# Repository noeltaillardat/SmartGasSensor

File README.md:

# SmartGasSensor
#### Arduino shield with gas sensing and LoRa connection.

On this github, you will find KiCad files to print your PCB and Arduino files to upload code to use the shield.

## Functionalities
* Gas sensor + Electrical noise reduction + Temperature setting
* Warning trigger + visual warning 
* LoRa communication + TTN connection
* Buzzer can be activated

### Gas sensor + Electrical noise reduction
Gas sensor made at the AIME whiteroom of Toulouse.

On the shield, filters are made to reduce the electrical noise. There is a passive filter to cancel HF noise at the start of the circuit. An active filter with an Op-Amp is on to be more efficient. The gain can be modified with the potentiometer named *PT1*.
A passive filter at the end of the circuit is used to filter noise induced by the circuit.

The temperature can be set to improve gas recognition with *Gas_Temp_Target*.
The feedback loop gain can be modified with the *PT2* potentiometer.

### LoRa communication + TTN connection
You will find as well *ttn_script.js* to use on the TheThingsNetwork console to decrypt the data.

The Arduino code needs to be updated with your app and network session key foundable on the TTN console.
The activation method needs to be set to ABP. 

### Warning trigger + visual warning 
The warning can be set with *Gas_Trigger_Offset* to set the estimated thresold value.

An hysteresis has been made to be sure that the warning do not go on and on multiple times. 
This can be set with *Gas_Trigger_Diff*.
In case of limited amplitude of the hysteresis, the potentiometers *PT3* and *PT4* can be changed to adapt it to your use.

A LED on board have visual indication of the warning

### Buzzer can be activated
A buzzer can be activated with a *analogWrite* command.

A usage would be to set it to ring when the warning goes on, or when the warning is on.
Another can be to ring when the LoRa connection fails.

## Routing & schematics

Below is the schematic of our shield, including all the features explained above.

From there, the routing of our shield is achieved as shown below:

Here, a 3D view (from Blender) of the shield:

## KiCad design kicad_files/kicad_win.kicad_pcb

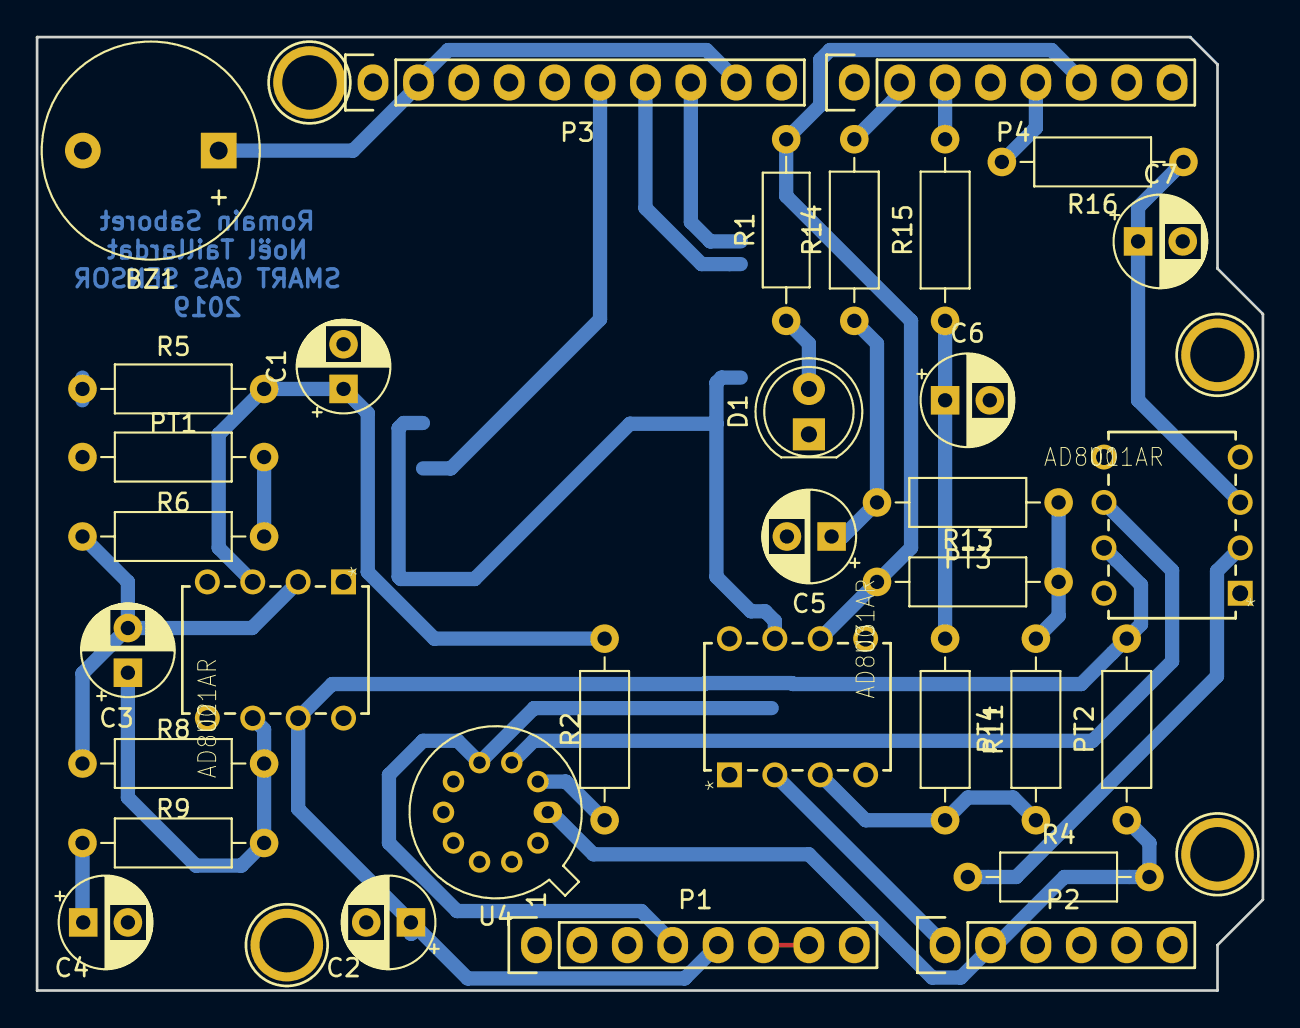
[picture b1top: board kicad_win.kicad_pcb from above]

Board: 2 copper layers, 68.6 x 53.3 mm, 38 parts (1 on the bottom side), 27 nets.

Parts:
BZ1: Device_Buzzer; Buzzer_12x9.5RM7.6
C1, C2, C4: 100n; CP_Radial_D5.0mm_P2.50mm
C3: 1u; CP_Radial_D5.0mm_P2.50mm
C5, C6, C7: 10u; CP_Radial_D5.0mm_P2.50mm
D1: LED; LED_D5.0mm
MODULE1: RN2483-I_RM095; MICROCHIP_RN2483-I%2fRM095
P1: Power; Socket_Strip_Arduino_1x08
P2: Analog; Socket_Strip_Arduino_1x06
P3: Digital; Socket_Strip_Arduino_1x10
P4: Digital; Socket_Strip_Arduino_1x08
P5, P6, P7, P8: CONN_01X01; Arduino_1pin
PT1, PT2: R; R_Axial_DIN0207_L6.3mm_D2.5mm_P10.16mm_Horizontal
PT3: 1k; R_Axial_DIN0207_L6.3mm_D2.5mm_P10.16mm_Horizontal
PT4: 10k; R_Axial_DIN0207_L6.3mm_D2.5mm_P10.16mm_Horizontal
R1, R4, R9, R13: 1k; R_Axial_DIN0207_L6.3mm_D2.5mm_P10.16mm_Horizontal
R2, R11, R14, R15, R16: 10k; R_Axial_DIN0207_L6.3mm_D2.5mm_P10.16mm_Horizontal
R5, R8: 100k; R_Axial_DIN0207_L6.3mm_D2.5mm_P10.16mm_Horizontal
R6: 500; R_Axial_DIN0207_L6.3mm_D2.5mm_P10.16mm_Horizontal
U1, U2, U3: AD8001AR; PDIP-8_N
U4: Gas_Sensor_TO-5-10; TO-5-10

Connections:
+3V3: MODULE1.12, MODULE1.34, P1.4, U3.7, U4.4
+5V: C2.1, P1.5, PT2.2, U1.7, U2.7
/2: P4.6, R1.2, R13.1, U3.6
/3(**): P4.5, R16.2
/5(**): P4.3, R15.2
/6(**): P4.2, R14.2
/9(**): BZ1.1, P3.2, P3.9
/10(**/SS): MODULE1.6, P3.8
/11(**/MOSI): MODULE1.7, P3.7
/12(MISO): MODULE1.32, P3.6
/A0: P2.1, U3.2
/A1: P2.2, PT2.1, R4.2, U4.1
/GasSens: R2.2, U4.2
/Gas_Temp_Target_Anal: C7.1, R16.1, U1.3
/Gas_Trigger_Diff_Anal: C5.1, PT3.2, R14.1
/Gas_Trigger_Offset_Anal: C6.1, PT4.1, R15.1
/Heater: U1.6, U4.3
GND: BZ1.2, C1.2, C2.2, C4.2, C5.2, C6.2, C7.2, D1.1, MODULE1.1, MODULE1.8, MODULE1.11, MODULE1.20, MODULE1.21, MODULE1.22, MODULE1.24, MODULE1.26, MODULE1.27, MODULE1.28, MODULE1.33, MODULE1.41, MODULE1.47, P1.6, P1.7, P3.4, PT1.1, R5.1, U1.4, U2.4, U3.4, U4.6, U4.8
unnamed: C1.1, R2.1, R5.2, U2.3
unnamed: C3.1, R8.2, R9.1, U2.6
unnamed: C3.2, R6.2, R8.1, U2.2
unnamed: C4.1, R9.2
unnamed: D1.2, R1.1
unnamed: PT1.2, R6.1
unnamed: PT3.1, R11.2, R13.2
unnamed: PT4.2, R11.1, U3.3
unnamed: R4.1, U1.2

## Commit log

2019-11-18 Small arduino program detecting our device
2019-11-19 Test file to connect and test with ABP
2019-11-19 Arduino file for transmitting gas value and warning
2019-11-19 Kicad de romain de base
2019-11-29 last actif kicad
2019-12-01 new version of the schematic
2020-01-21 Complete electronic circuits
2020-01-22 script of ttn console
2020-01-22 probably final
2020-01-22 a bit better
2020-01-22 is it good?
2020-01-22 might be good
2020-01-22 Add images
